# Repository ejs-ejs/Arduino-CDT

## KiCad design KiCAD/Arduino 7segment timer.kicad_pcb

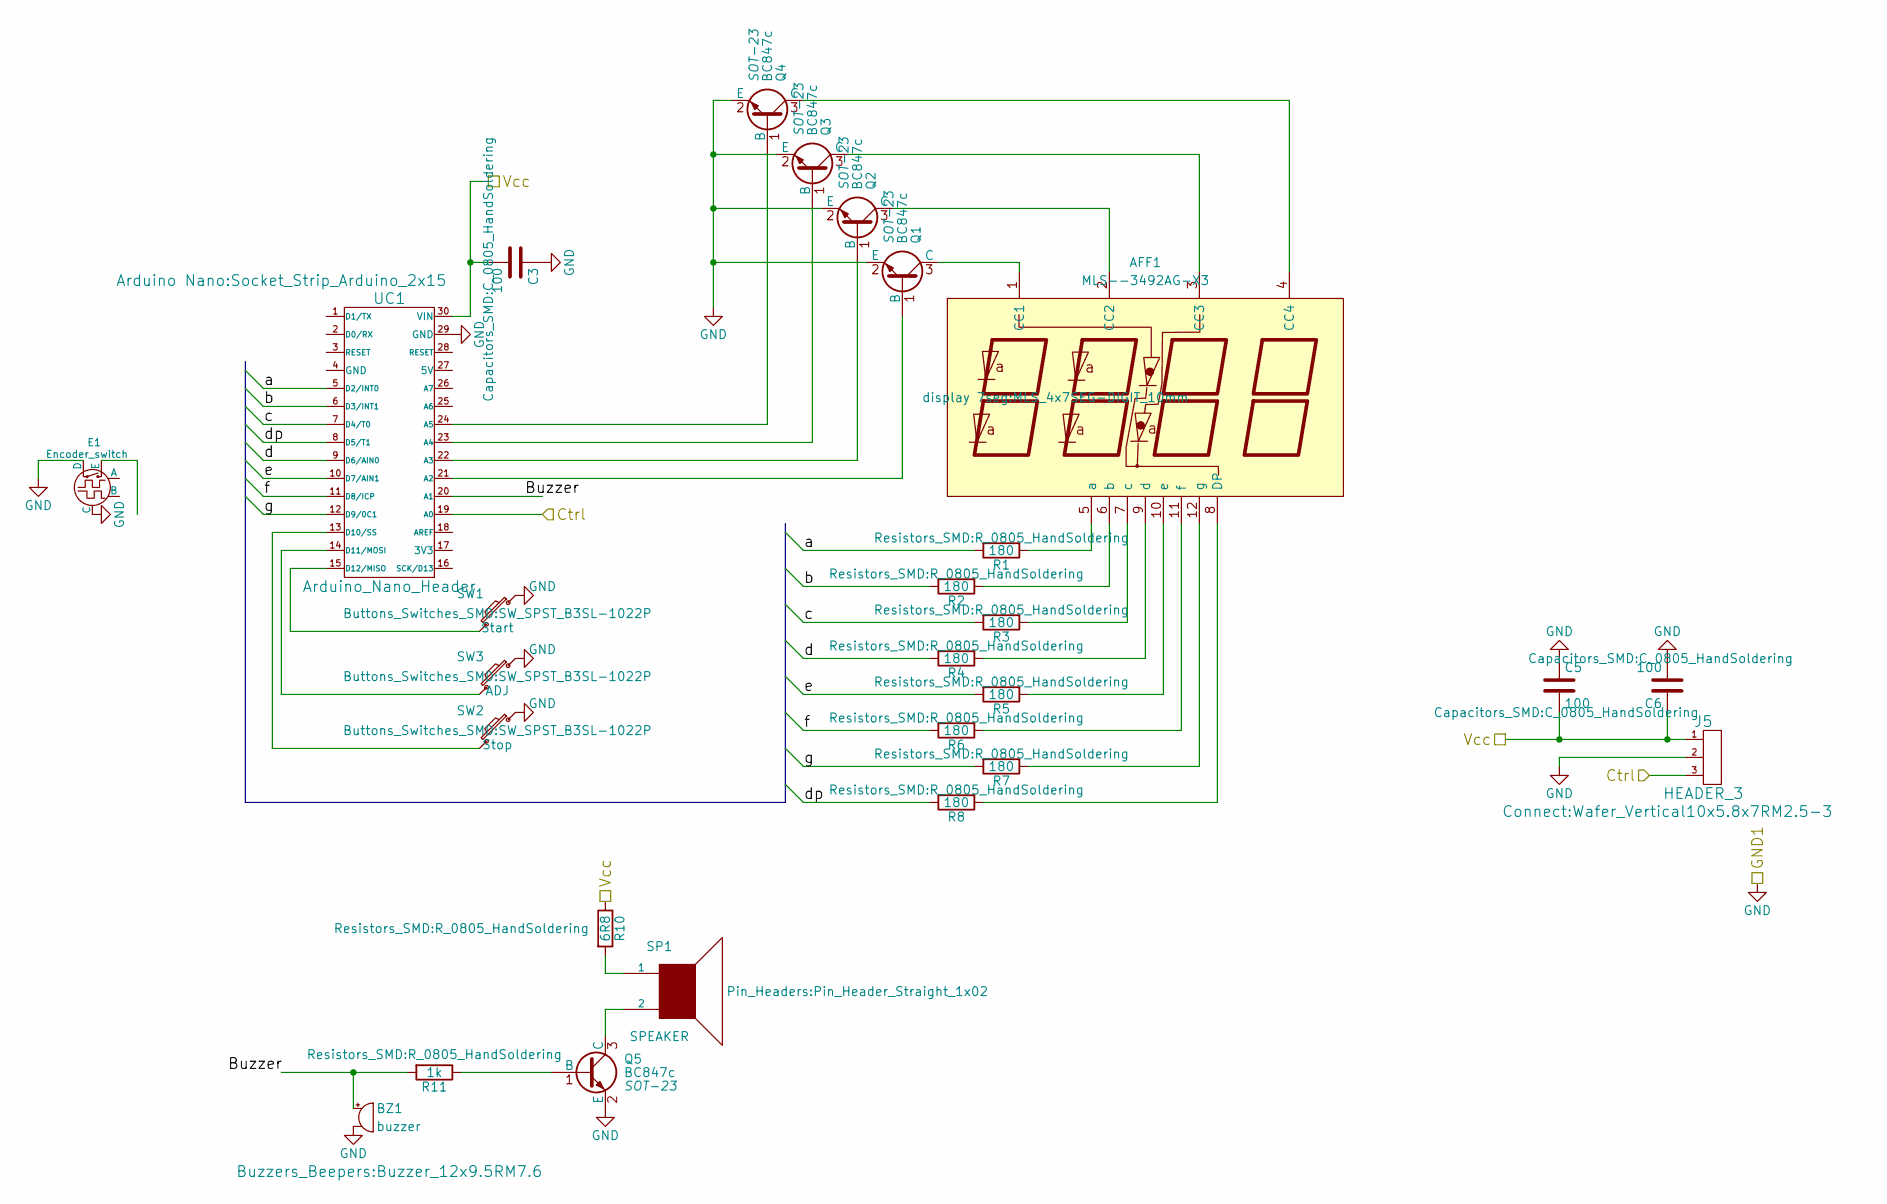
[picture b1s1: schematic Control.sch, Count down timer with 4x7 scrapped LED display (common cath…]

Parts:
AFF1: MLS--3492AG-X3; MLS_4x7SEG-DIGIT_10mm
BZ1: buzzer; Buzzer_12x9.5RM7.6
C3, C5, C6: 100; C_0805_HandSoldering
E1: Encoder_switch
J5: HEADER_3; Wafer_Vertical10x5.8x7RM2.5-3
Q1, Q2, Q3, Q4, Q5: BC847c; SOT-23
R1, R2, R3, R4, R5, R6, R7, R8: 180; R_0805_HandSoldering
R10: 6R8; R_0805_HandSoldering
R11: 1k; R_0805_HandSoldering
SP1: SPEAKER; Pin_Header_Straight_1x02
SW1: Start; SW_SPST_B3SL-1022P
SW2: Stop; SW_SPST_B3SL-1022P
SW3: ADJ; SW_SPST_B3SL-1022P
UC1: Arduino_Nano_Header; Socket_Strip_Arduino_2x15

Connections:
/Control/Ctrl: J5.3, UC1.19 (A0); also elsewhere on the board
/Control/Vcc: C3.2, C5.2, C6.1, J5.1, R10.1, UC1.30 (VIN); also elsewhere on the board
/Control/a: R1.2, UC1.5 (D2/INT0)
/Control/b: R2.2, UC1.6 (D3/INT1)
/Control/c: R3.2, UC1.7 (D4/T0)
/Control/d: R4.2, UC1.9 (D6/AIN0)
/Control/dp: R8.2, UC1.8 (D5/T1)
/Control/e: R5.2, UC1.10 (D7/AIN1)
/Control/f: R6.2, UC1.11 (D8/ICP)
/Control/g: R7.2, UC1.12 (D9/0C1)
GND: BZ1.2, C3.1, C5.1, C6.2, E1.2 (C), E1.5 (D), J5.2, Q1.2 (E), Q2.2 (E), Q3.2 (E), Q4.2 (E), Q5.2 (E), SW1.1, SW2.1, SW3.1, UC1.29 (GND); also elsewhere on the board
unnamed: AFF1.1 (CC1), Q1.3 (C)
unnamed: AFF1.2 (CC2), Q2.3 (C)
unnamed: AFF1.3 (CC3), Q3.3 (C)
unnamed: AFF1.4 (CC4), Q4.3 (C)
unnamed: AFF1.5 (a), R1.1
unnamed: AFF1.6 (b), R2.1
unnamed: AFF1.7 (c), R3.1
unnamed: AFF1.8 (DP), R8.1
unnamed: AFF1.9 (d), R4.1
unnamed: AFF1.10 (e), R5.1
unnamed: AFF1.11 (f), R6.1
unnamed: AFF1.12 (g), R7.1
unnamed: Q1.1 (B), UC1.21 (A2)
unnamed: Q2.1 (B), UC1.22 (A3)
unnamed: Q3.1 (B), UC1.23 (A4)
unnamed: Q4.1 (B), UC1.24 (A5)
unnamed: Q5.1 (B), R11.1
unnamed: Q5.3 (C), SP1.2
unnamed: R10.2, SP1.1
unnamed: SW1.2, UC1.15 (D12/MISO)
unnamed: SW2.2, UC1.13 (D10/SS)
unnamed: SW3.2, UC1.14 (D11/MOSI)

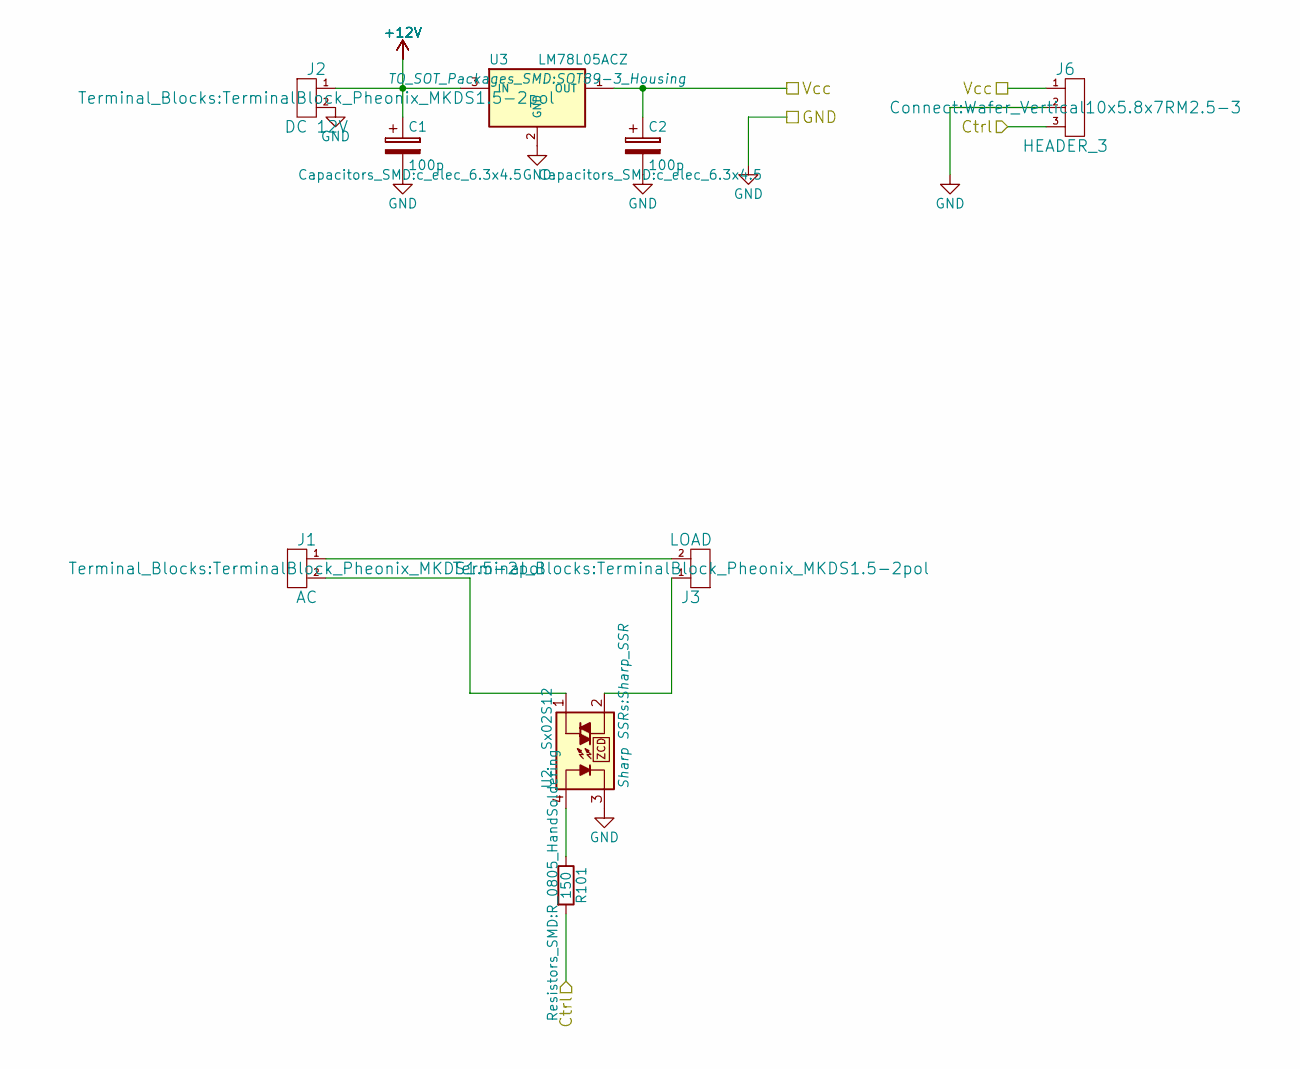
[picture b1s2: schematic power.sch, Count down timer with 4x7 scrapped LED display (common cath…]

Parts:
C1, C2: 100p; c_elec_6.3x4.5
J1: AC; TerminalBlock_Pheonix_MKDS1.5-2pol
J2: DC 12V; TerminalBlock_Pheonix_MKDS1.5-2pol
J3: LOAD; TerminalBlock_Pheonix_MKDS1.5-2pol
J6: HEADER_3; Wafer_Vertical10x5.8x7RM2.5-3
R101: 150; R_0805_HandSoldering
U2: Sx02S12; Sharp_SSR
U3: LM78L05ACZ; SOT89-3_Housing

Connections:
+12V: C1.1, J2.1, U3.3 (IN)
/Control/Ctrl: J6.3, R101.2; also elsewhere on the board
/Control/Vcc: C2.1, J6.1, U3.1 (OUT); also elsewhere on the board
GND: C1.2, C2.2, J2.2, J6.2, U2.3, U3.2 (GND); also elsewhere on the board
unnamed: J1.1, J3.2
unnamed: J1.2, U2.1
unnamed: J3.1, U2.2
unnamed: R101.1, U2.4

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
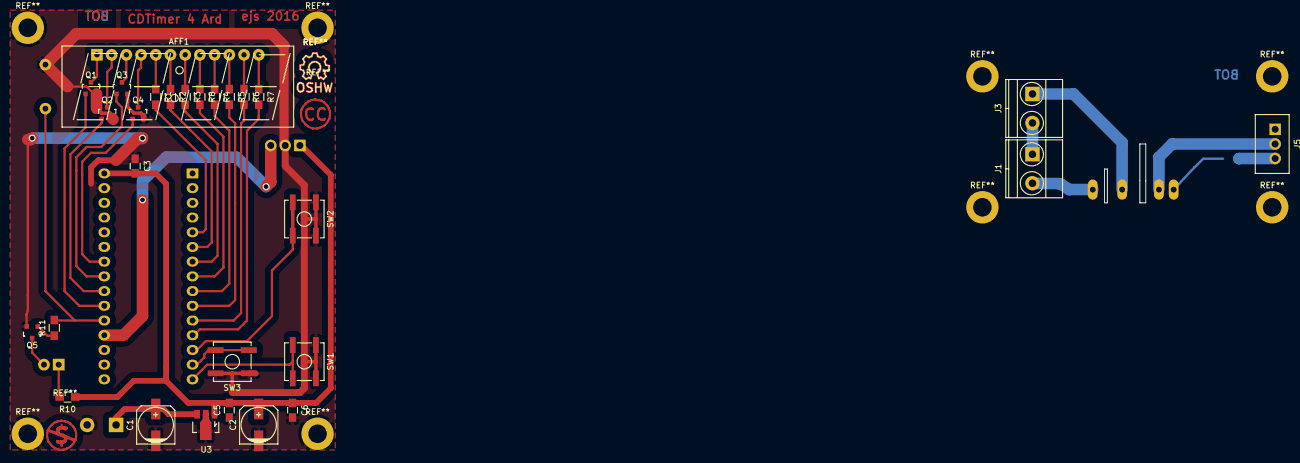
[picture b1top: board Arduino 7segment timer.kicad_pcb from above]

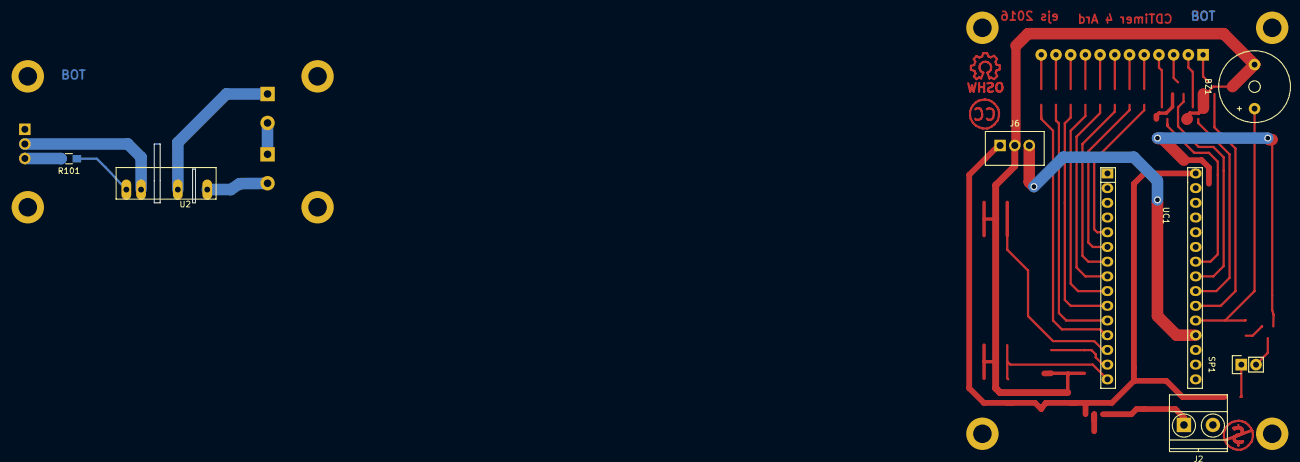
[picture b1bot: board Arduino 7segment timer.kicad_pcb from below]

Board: 2 copper layers, 35 parts (7 on the bottom side), 39 nets.

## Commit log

2016-07-23 :octocat: Added .gitattributes & .gitignore files
2016-07-23 Mimimal working example
2016-07-24 KiCAD files
    KiCAD files. Should match the Arduino sketch. Will chekc on Monday.
2016-07-24 PCB updated
    to include CC and OSH logos
2016-07-24 Schematics
    placed on PDF file
